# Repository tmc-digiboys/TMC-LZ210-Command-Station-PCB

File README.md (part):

[🇬🇧 English](README.md) | [🇩🇪 Deutsch](README.de.md) | [🇳🇱 Nederlands](README.nl.md)

# DCC Command Station LZ210-TMC

Modular DCC command station with Ethernet and USB connectivity, and (partial) support for the XpressNet and Z21 protocols. The board supports LocoNet-T and XpressNet handhelds and other equipment, provides an interface for external boosters via CDE and LocoNet-B, and has a connection for RS-Bus feedback modules.

## Why this board
The [Twentse Modelspoorweg Club (TMC)](https://twentsemodelspoorweg.club) is modernising its electronics and software for digital layout control. For each of its stations (Hengelo, Enschede, Oldenzaal, Almelo) it needs its own new DCC command station to operate all turnouts and signals, and to receive occupancy feedback. Although DCC command stations are of course available ready-made, building your own is not only a nice challenge, but also a potential cost saving.

The starting point is a modular design, similar to the [Z21PG](https://pgahtow.de/w/Zentrale_Z21PG/de). Initially we looked at whether we could simply adapt or replicate this design. We quickly realised that upgrading to a modern processor and ready-made modules would lead to better results and a lower price.

The goal is to develop a command station that can be extended step by step and that **club members and other interested persons can easily adapt and rebuild**. That is why we deliberately chose an easy-to-solder, low-cost THT (Through-Hole Technology) PCB, and, for the critical components, ready-made modules that can easily be bought online.

For the processor we chose the RP2350B, mainly because of its PIO peripheral, which allows a fully jitter-free DCC signal to be generated. It is an inexpensive and modern dual-core processor, running at 125 MHz. See [processor choice](docs/processor.md) for a comparison with ESP32, DxCore and STM32.

The name LZ210-TMC was chosen as a contraction of Z21 (Roco, Z21 protocol, LocoNet) and LZ100 (Lenz, XpressNet, RS-Bus interface and CDE booster connection).

## Schematic
The complete schematic (all hierarchical sheets) is available in [Schematic.pdf](docs/Schematic.pdf).

The schematic is divided into the following functional blocks (click the name for more details):

<details>
<summary><strong>Power supply</strong></summary>

The command station must be powered with a DC voltage equal to the desired track voltage. In practice, a switching or laptop-style power supply can be used that can deliver a voltage between 14 and 20 volts, and 3 to 4 amps.

⚠️ **Note:** not every switching power supply is suitable or safe for this purpose. Practical advice: choose a power supply of the kind used with other DCC command stations, for example the [Roco 10851](https://www.roco.cc/rde/10851-schaltnetzteil-54-watt.html) or [YaMoRC YD7460-18](https://yamorc.de/products/?singleproduct=13843).

The external supply voltage enters via a 3 amp eFuse and a so-called "ideal diode", which protects the circuit against reverse polarity, and then feeds VCC and two step-down converter modules.

VCC powers the H-bridges for the track voltage and the programming track. VCC also runs to the processor, so that a resistor divider and an ADC input can be used to check whether the external supply voltage has the correct value.

The 12V step-down converter supplies power to LocoNet, XpressNet, the CDE booster interface, and RS-Bus feedback. The 12V voltage is likewise, for monitoring purposes, fed through a resistor divider to an ADC input.

The choice of the 5V step-down converter requires some explanation, because the processor and peripherals actually expect 3V3. The reason 5V was chosen is that the Olimex RP2350 Pico2-XL module already has its own step-down chip on board. An external 3V3 converter must *not* be connected to the 3V3 output of the Olimex module (see below). The output of the Olimex module does deliver enough power to supply the rest of the peripherals with 3V3. The diode between the 5V step-down converter and the Olimex RP2350 Pico2-XL module prevents damage from occurring if, in addition to the external supply, power is also being supplied via the USB connector.

><details>
><summary>Explanation: why not an external 3V3 on the Olimex module?</summary>
>
> The TPS62A02A chip on the Olimex module has active output discharge: as soon as the TPS62A02A is switched off (for example by pulling 3V3_EN to GND), an internal FET is switched on to actively discharge the energy still stored in the external inductor. If, in that state, 3.3V is nevertheless applied to the output of the TPS62A02A, the internal FET keeps conducting and draws tens of mA from the external supply. This can cause the SOT-563 package to overheat. This behaviour is also described on [TI's E2E forum](https://e2e.ti.com/support/power-management-group/power-management/f/power-management-forum/1305135/tps62a01-active-output-discharge).
>
> Hence the choice to feed not the 3V3 output but the VSYS input. This keeps the onboard TPS62A02A always active, regardless of whether power comes from the 5V step-down converter or from USB. The TPS62A02A can deliver enough power to also supply the remaining peripherals.
>
> This behaviour differs from the original Raspberry Pi Pico2: that board uses the RT6150B as its step-down converter, which does not have this active output discharge. On the Pico2, pulling 3V3_EN to GND and then applying an external 3.3V to the output is in fact the method documented by Raspberry Pi itself. For other RP2350B modules: always check which step-down converter is fitted first, since behaviour can differ per board.
>
> </details>

</details>

<details>
<summary><strong>Processor</strong></summary>

We chose a Raspberry Pi Pico processor; see [processor choice](docs/processor.md) for details. An important advantage of the Raspberry Pi Pico is that it has a Programmable IO (PIO) peripheral, a specialised co-processor that can generate very precisely timed output signals.

Within the Pico series there are two variants: the RP2040, with two PIOs, and the RP2350, with three PIOs. Because we use three PIOs, we chose the RP2350. The first PIO is used for the DCC signal, the second for the RS-Bus master, and the third for the XpressNet RS-485 connection.

The RP2350 in turn comes in two variants: the "plain" RP2350, which has 30 General Purpose IO (GPIO) pins, and the RP2350B, which has 18 more. For an early test version of the command station the "plain" RP2350 was used, but because we wanted to use more IO pins we ultimately chose the RP2350B.

Several suppliers (such as Olimex, Waveshare and WeAct) offer different RP2350B modules. We chose the RP2350B-X(X)L module from Olimex; see the reasoning below under Building.

><details>
><summary>Explanation: are alternative modules possible?</summary>
>
> If fewer pins and fewer PIOs are needed — for example because there is no need for an RS-Bus master or XpressNet — RP2040 modules can also be used. In that case, the PCB layout and possibly the power supply would need to be adapted.
>
> </details>

><details>
><summary>Explanation: why a PIO for XpressNet?</summary>
>
> On most processors it is possible to use a UART to send and receive XpressNet messages. That works because the UART on many processors supports both 8 and 9 data bits. XpressNet, however, requires 9 data bits (where the ninth bit indicates whether it is an address or a data byte). Compared with other processors, the UART on the Raspberry Pi Pico is relatively limited and only supports 8 data bits. By writing a small PIO program, it is nevertheless possible to work with 9 data bits on the Raspberry Pi Pico as well, and so support XpressNet.
>
> It would in principle be possible, with some tricks, to still use the UART on the Raspberry Pi Pico for XpressNet. However, since there are only two UARTs, we decided against this.
>
> </details>

</details>

<details>
<summary><strong>Ethernet</strong></summary>

The Ethernet schematic contains only the WIZnet W5500 module. All pins are wired through to the processor.

The older (and often more expensive) W5100 and W5100S modules will probably also work, but this has not been tested.

</details>

<details>
<summary><strong>Track output</strong></summary>

The DCC signal is amplified by a DRV8874 module, fitted with the same driver IC that is also used in the DCC-EX project.

The schematic contains few components because the module itself already contains a number of resistors that result in settings usable for our command station.

By default, I<sub>TRIP</sub> is set to approximately 3 amps. If desired, a different value can be chosen by removing the 2.49 kΩ resistor on the module and fitting R601 with a different value.

By default, **PMODE** is connected to 3V3, which activates PWM mode. If desired, the "PWM (PH / EN) solder jumper" on the bottom of the PCB can be used to connect **PMODE** to GND instead. To do this, remove the existing copper connection to 3V3 to avoid a short circuit, and make the other solder connection to GND.

By default, the module is set to Quad-Level 2, but this can be changed via a second "solder jumper" on the bottom of the PCB by connecting **IMODE** to GND. See the DRV8874 datasheet for the differences between the modes.

No space has been reserved on the PCB for a snubber circuit and/or power inductor. If desired, these can be placed after the connector, in the wiring to the rails.

Detailed background information on the choice and limitations of this driver IC is described on a separate page. That page discusses in detail the inrush-current problems that this and similar chips can have with capacitive loads. See: [DRV8874 output stage](docs/DRV8874.md)

How overcurrent faults (OCP and ITRIP) show up on the **nFAULT** pin, how the processor handles them, and which value of the sense resistor is recommended, is described in [Dealing with nFAULTs](docs/nFault.md).

</details>

<details>
<summary><strong>Programming track</strong></summary>

The PCB allows you to use the same DRV8874 H-bridge module as for the normal track output. The advantage of reusing modules is a uniform parts list and easier building.

However, it is better to use a DRV8876 module instead of a DRV8874 module. These modules can deliver somewhat less power, which is actually an advantage for a programming track, and they are also somewhat cheaper.

An important technical difference between the DRV8874 and DRV8876 modules is that the latter has a higher current-mirror gain factor **AIPROPI**, namely 1000 (instead of 450). As a result, the voltage seen by the processor's ADC input during a (60 mA) DCC-ACK signal is 150 mV (instead of 67 mV). This allows a more reliable measurement of the DCC-ACK signal.

As with the normal track output, it is possible to remove the 2.49 kΩ resistor fitted by default on the module and replace it with R801. A good value for R801 is 6.8 kΩ. With this value, the maximum current I<sub>TRIP</sub> that can be delivered during programming is limited to 500 mA. RCN-216 recommends a (non-mandatory) limit of 250 mA ±20% at power-up, but also permits fixed current limiters up to 1 A; 500 mA fits comfortably within that.

An additional advantage of replacing the 2.49 kΩ resistor with a 6.8 kΩ resistor is that the voltage during a DCC-ACK is increased to well over 400 mV, making it easier to measure on the processor's ADC input.

</details>

<details>
<summary><strong>CDE booster interface</strong></summary>

The PCB uses the same type of H-bridge module as for the programming track (DRV8876 or DRV8874). Technically, a DRV8871 module from AliExpress could also be used. However, the dimensions of this module do not fit the current PCB.

For the CDE output, the well-known inrush-current problems of the DRV887x ICs do not apply. The load is not capacitive, and the CDE signal requires no more than a few hundred milliamps. The internal short-circuit protection of the DRV887x does not trigger during start-up, unless the output is genuinely short-circuited. The DRV887x is oversized for this purpose, but can in principle be used without issue.

Detailed information about the CDE interface is described on a separate page: [CDE interface](docs/CDE.md).

</details>

<details>
<summary><strong>LocoNet</strong></summary>

The schematic for the LocoNet section is standard, and described in many places online. However, the values of a number of components have been adapted so that the whole works on 3V3 as well.

In addition to the LocoNet-T interface, there is also a LocoNet-B interface, which supplies a RailSync signal for boosters via the outermost pins of the connector. The RailSync signal can be generated in several ways.

- Up to and including V2.2, a design was used that was copied from the Internet (https://www.fucik.name/masinky/NanoL/, https://oshwlab.com/fiorinid/z21pg-by-df-pro). These circuits utilise a specialised driver IC; the diagram lists a number of options. Of the options listed, only the UCC27425 IC has an ENABLE input, which allows the RailSync signal to be easily disabled. Resistors rated at 33 Ω / 2 Watt (or preferably 22 Ω / 5 Watt) are connected to the outputs of this driver. On the one hand, these resistors serve as short-circuit protection (which is why they must be capable of dissipating 2 to 5 Watt). On the other hand, these resistors, together with the 4.7 nF capacitors, form a low-pass filter, thus reducing interference. The P6KE15A are ESD diodes that protect the LocoNet driver IC. The disadvantage of this circuit is that it cannot supply more than 100 mA, which limits the maximum number of boosters that can be connected to approximately 10, depending on the type of booster.

- From version 2.3 onwards, RailSync uses the CD(E) (booster) signal. This not only reduces the number of components required (thereby lowering costs), but also allows a much larger number of boosters to be connected. Furthermore, all connected boosters now have exactly the same signal, regardless of whether they are connected via CDE or via LocoNet-T.

</details>

<details>
<summary><strong>XpressNet</strong></summary>

The XpressNet interface is simple and standard. The [OpenDCC site](https://www.opendcc.de/elektronik/opendcc/xpressnet_hw.html) has a basic circuit that many have built. The only change is that the 1K5 resistors have been replaced with 560 Ω, because the driver IC is powered not from 5V but from 3V3. The 8K2 resistor (R504) ensures the driver starts in RX mode.

A MAX(3)485 IC is often used as the driver. A better choice is the MAX(3)483, the slew-rate-limited version of this driver, since it limits possible high-frequency interference on the RS-485 line. Unfortunately, this IC is noticeably more expensive. The OpenDCC page mentioned above gives further details on possible alternative driver ICs.

</details>

<details>
<summary><strong>RS-Bus feedback</strong></summary>

The schematic for the RS-Bus was taken from the [Der-Moba website](https://www.der-moba.de/index.php/RS-Rückmeldebus).
The transistor for transmitting mentioned there has, however, been replaced with an (IRLZ44) MOSFET, allowing for a somewhat higher load.

</details>

## Building
To build the command station, the easiest approach is to have the current PCB manufactured by sending the file [production/TMC-Centrale.zip](production/TMC-Centrale.zip) to a company such as JLCPCB. This file contains all the (Gerber) files the manufacturer needs. In the summer of 2026, having 5 PCBs made, including shipping, cost approximately €25.

The design is open source. Building, modifying, and distributing is encouraged under the terms of the [licence](LICENSE), and with reference to this source.

The complete list of components is: [production/bom.csv](production/bom.csv).

To make building as easy as possible, we chose, wherever possible, ready-made modules of the kind sold online by AliExpress and others. Below is an overview of the main modules, as well as the connectors that fit the PCB:

<details>
<summary><strong>RP2350B (MCU module)</strong></summary>

For the processor we chose the [Olimex RP2350B-XL](https://www.olimex.com/Products/RaspberryPi/PICO/PICO2-XXL/open-source-hardware) module. Olimex guarantees that production of these modules will be supported until at least 2035, and has published all KiCad design files and manufacturing files openly on GitHub.

There are two variants of this module: the RP2350B-XL (€5) and the RP2350B-XXL (€9). The difference is that the XXL has some extra capabilities that are not needed for this command station. Although the schematic references the XXL, the XL variant is preferred for its price. Both variants fit the PCB, however.

The modules can be bought from [Olimex](https://www.olimex.com/Products/RaspberryPi/PICO/PICO2-XXL/open-source-hardware) directly, but also via distributors such as [TME](https://www.tme.eu).

</details>

<details>
<summary><strong>DRV8874 / DRV8876 (motor drivers)</strong></summary>

Ready-made DRV8874 / DRV8876 modules are used for the DCC, programming track, and CDE outputs.

Pololu brought modules for the [DRV8874](https://www.pololu.com/product/4035) and [DRV8876](https://www.pololu.com/product/4037) to market some years ago. Since spring 2026, (cheaper) variants have also become available on AliExpress. The Pololu module includes an extra reverse-polarity-protection MOSFET as additional protection, which the AliExpress modules lack. This extra protection is not needed for this command station.

</details>

<details>
<summary><strong>Step-down module (5V/12V)</strong></summary>

The PCB footprint dimensions are matched to the well-known MP1584 step-down modules, offered by multiple suppliers on AliExpress. Two modules are needed. The first supplies the 5V supply voltage for the processor (note: the Olimex processor module itself converts this 5V to 3V3 again), and the second module supplies 12V. Instead of modules with a fixed 5V/12V output voltage, adjustable-output modules can also be used.

Modules other than the MP1584 will in principle also work, but do not fit the PCB footprint.

</details>

<details>
<summary><strong>Ideal-diode module</strong></summary>

An XL74610 module is used for reverse-polarity protection, as sold on AliExpress and by other suppliers.

</details>

<details>
<summary><strong>W5500 Ethernet</strong></summary>

A W5500 module is used for the Ethernet connection, as sold on AliExpress and by other suppliers.

</details>

<details>
<summary><strong>Connectors</strong></summary>

The PCB is designed for the following connectors:

><details>
><summary>LocoNet: 6P6C (RJ12)</summary>
>
> There are several brands and types of 6P6C connectors on the market, with different footprints. The PCB is designed for connectors with a footprint matching the WayConn MJEA connectors. These have their electrical connections on the bottom (PCB side).
> 
>
> </details>
><details>
><summary>Barrel Jack</summary>
>
> A 5.5x2.1mm barrel jack is used for the power connector.
> 
>
> </details>
><details>
><summary>Terminal Blocks</summary>
>
> A PhoenixContact MSTBA 2.5/2-G, with a pin spacing of 5.00 mm, is used for the DCC track output. Terminal blocks with a pin spacing of 5.08 mm will also fit, however.
>
> A Phoenix Contact MC 1.5/2-G-3.81 terminal block is used for the programming output.
>
> A Phoenix Contact MC 1.5/3-G-3.81 terminal block is used for the CDE output.
>
> A Phoenix Contact MC 1.5/2-G-3.81 terminal block is used for the RS-Bus input.
>
> A Phoenix Contact MC 1.5/4-G-3.81 terminal block is used for the XpressNet output. A 5-pin DIN connector is fitted at the front.
>
> Variants of these connectors are offered by several manufacturers, including PTR/Hartmann.
>
> 
>
> </details>

</details>

## Software

The firmware for this command station can be found in its own GitHub repository, and is therefore not discussed further at: [https://github.com/tmc-digiboys/TMC-LZ210-Command-Station](https://github.com/tmc-digiboys/TMC-LZ210-Command-Station)

## Comparison with other command stations

This command station does not stand on its own, but stands in a long tradition of open-source DCC command stations:

<details>
<summary><strong>OpenDCC</strong></summary>

One of the earliest open-source DCC command stations is the [OpenDCC Z1](https://www.opendcc.de/elektronik/opendcc/opendcc.html). This command station was designed twenty years ago by Wolfgang Kufer.
- **Processor.** OpenDCC runs on an 8-bit Atmel AVR (ATmega32 or ATmega644P) at 16 MHz. This command station uses a dual-core RP2350 at 125 MHz with a PIO peripheral, and is therefore orders of magnitude more powerful.
- **Output stage.** OpenDCC uses a fixed H-bridge (STM L6206), theoretically rated at 2.8 A per output, but thermally limited on the PCB to about 1.5 A continuous. This command station uses a DRV8874 module (6 A theoretical), whose current is limited on the module itself to about 2.7 A.
- **Feedback.** OpenDCC supports S88, with an extension for turnout-position feedback. This command station uses RS-Bus and LocoNet.
- **Connection to a PC.** OpenDCC communicates via RS232/USB with a PC, using XpressNet or P50X as the higher-layer protocol; OpenDCC itself has no network or WiFi connection. This command station has, in addition to USB, its own Ethernet connection, and supports XpressNet and Z21 as higher-layer protocols.
- **Boosters.** OpenDCC has no separate interface for external boosters, such as CDE or LocoNet-B.
- **Handhelds.** Like this command station, OpenDCC supports XpressNet handhelds (such as the Roco Multimaus). OpenDCC does not support LocoNet handhelds, however.

The OpenDCC Z1 command station can be seen as a forerunner of open-source DCC command stations. Many of its ideas, circuits, and software have been copied (in adapted form) by others, and are still in use today. However, building the Z1 today no longer seems like a good idea: modern microcontrollers are both cheaper and many times more powerful than the 8-bit ATmega generation on which the OpenDCC Z1 was based at the time.
</details>

<details>
<summary><strong>BiDiB</strong></summary>

[BiDiB](https://www.bidib.org/) can be seen as a successor to the OpenDCC Z1 command station. BiDiB has been developed since 2010 by — again — Wolfgang Kufer, and is brought to market in hardware form by, among others, Fichtelbahn.
- **Architecture.** BiDiB is primarily a bus onto which multiple intelligent components (such as GBMboost/GBM16T/OpenSwitch/IF2) can be connected. It is not a command station in the traditional sense, with a built-in booster and interfaces such as XpressNet, LocoNet and RS-Bus.
- **Processor.** BiDiB implementations are based on the Atmel XMEGA processor. Although this is one of the most powerful 8/16-bit / 32 MHz processors, it is also a fairly old processor and, compared with the dual-core RP2350 / 125 MHz processor of this command station, quite expensive.
- **Building.** BiDiB PCBs are designed for SMD components. Although BiDiB designs are more advanced and of higher quality than those of this (THT) command station, they are also harder to build, adapt and extend.
- **RailCom.** BiDiB excels at receiving, analysing and processing RailCom feedback. This command station offers no support for this.

BiDiB offers a complete ecosystem with a focus on intelligent components and extensive RailCom processing. This command station is primarily a traditional command station like those from Roco and Lenz, communicating via established protocols with equipment from various manufacturers.

</details>

<details>
<summary><strong>Z21PG</strong></summary>

[Z21PG](https://pgahtow.de/w/Zentrale_Z21PG/) is an Arduino-based self-build project by Philipp Gahtow for a low-cost Roco Z21 clone.
- **Ease of building.** Philipp Gahtow himself publishes mainly software (Arduino sketches) and separate schematics for a number of hardware variants (Arduino MEGA, ESP32, ...). Unlike this command station, there is no official Z21PG (KiCad) PCB design. Third-party PCB designs do exist for the Z21PG, however. Both command stations are easy to build.
- **Processor and DCC signal.** The most commonly built Z21PG variant runs on an (older) ATmega2560 (16 MHz), although ESP32 is also mentioned as an option. The DCC signal is generated in software via timer interrupts, not via a dedicated hardware peripheral. This command station uses a (modern) dual-core RP2350 at 125 MHz with a PIO peripheral, more than ten times as fast and with a jitter-free DCC signal.
- **Interfaces.** Z21PG offers connections comparable to the Roco Z21 command station: LAN, X-Bus (XpressNet), L-Bus (LocoNet-T), booster connection, track and programming output. This command station additionally has an RS-Bus connection, and its booster connections are compatible with CDE and LocoNet-B.

Of all the projects discussed here, Z21PG has the most in common with this command station. Both are modularly designed and relatively easy and cheap to build. Z21PG primarily takes the Roco Z21 as its model, whereas this command station also takes the Lenz command stations as a model. Z21PG is a somewhat older design; this command station uses more modern components.
</details>

<details>
<summary><strong>DCC-EX</strong></summary>

A currently popular self-build command station is [DCC-EX](https://dcc-ex.com/). There are functional similarities (including the DRV8874 output stage), but also a number of significant differences:
- **Availability.** DCC-EX offers both factory-assembled boards (EX-CSB1, from approx. €75–115 excl. VAT/shipping) and DIY builds on Arduino form-factor boards. This command station is intended for self-building, and its component cost is lower (approx. €40).
- **Connection to a PC/network.** This command station uses Ethernet (XpressNet and Z21); DCC-EX uses WiFi (with JMRI, WiThrottle and Engine Driver support).
- **Interfaces for handhelds.** This command station has native (RS485) XpressNet and LocoNet interfaces, to which Lenz, Roco and other handhelds can be connected. DCC-EX focuses primarily on WiFi throttles and JMRI.
- **Interfaces for feedback.** This command station has native RS-Bus and LocoNet interfaces. DCC-EX has no such interfaces.
- **Booster interfaces.** This command station supports external boosters via LocoNet-B and the CDE interface. DCC-EX has no CDE/LocoNet-B support, but does have a RailSync mechanism, through which external boosters can be connected.
- **Mixed DCC/DC operation.** DCC-EX can switch each output between DCC and DC PWM, so that classic DC locomotives can run as well. This command station supports DCC only.

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
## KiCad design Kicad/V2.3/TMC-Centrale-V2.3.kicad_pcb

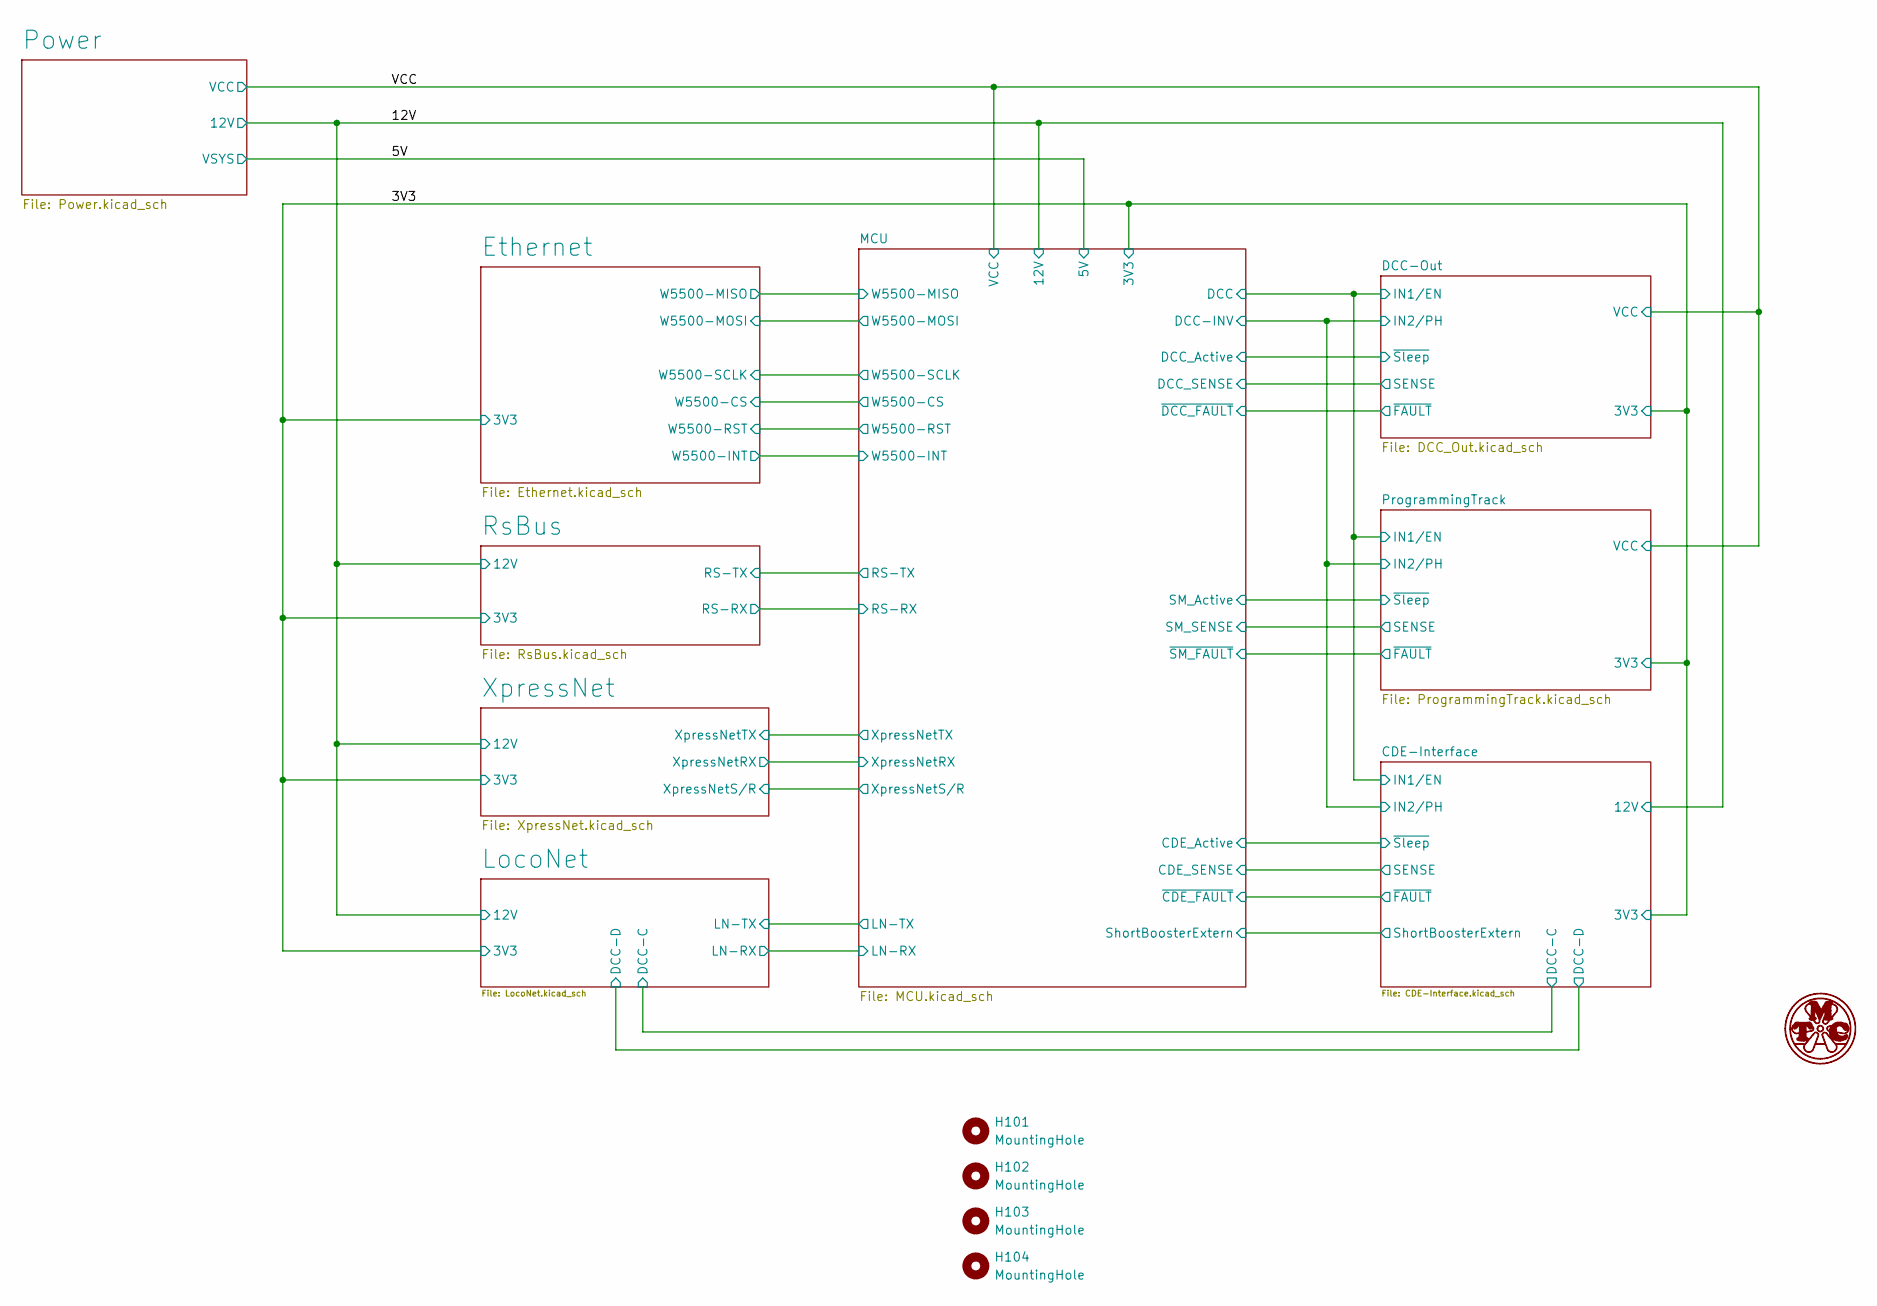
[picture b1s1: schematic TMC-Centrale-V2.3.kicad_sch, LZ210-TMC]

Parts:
H101, H102, H103, H104: MountingHole; MountingHole_3.2mm_M3

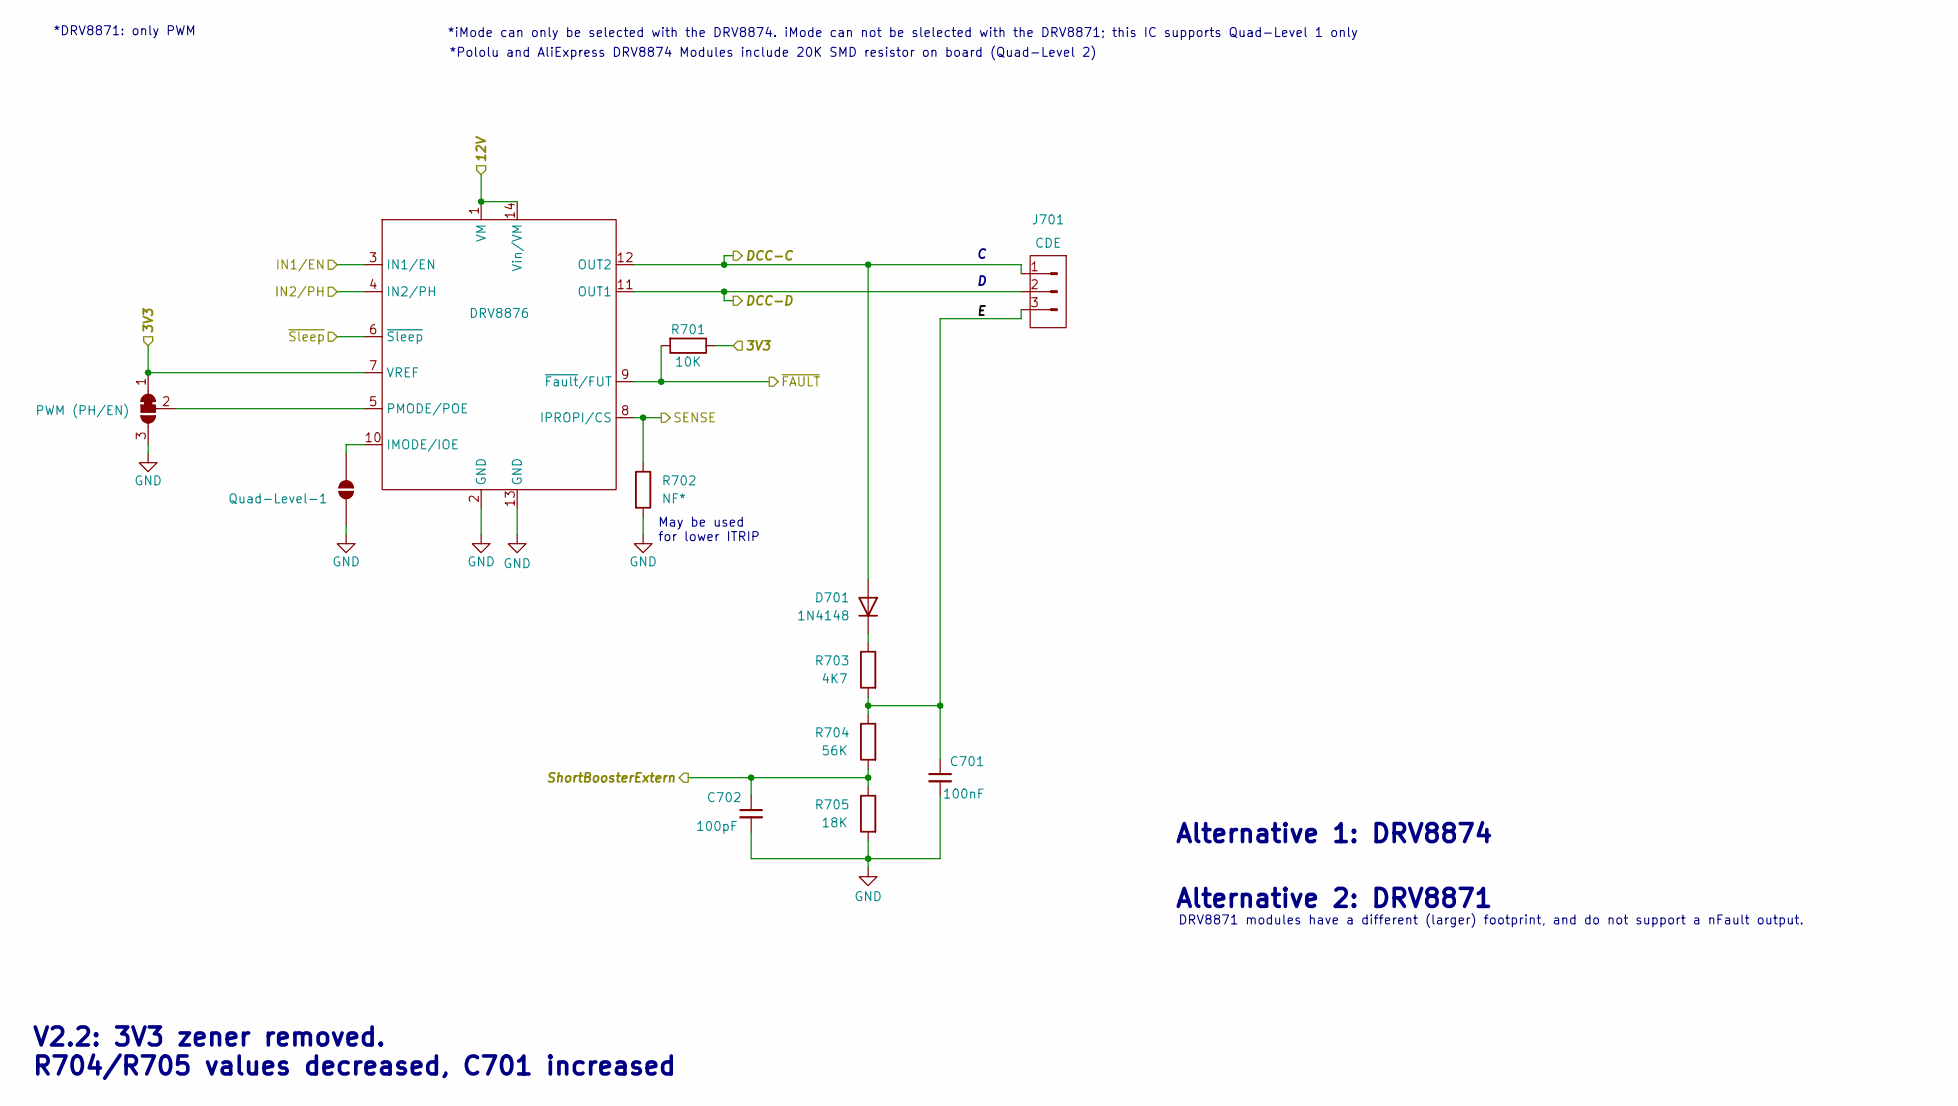
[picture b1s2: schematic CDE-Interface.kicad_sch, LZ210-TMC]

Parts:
C701: 100nF; C_Disc_D5.0mm_W2.5mm_P5.00mm
C702: 100pF; C_Disc_D5.0mm_W2.5mm_P5.00mm
D701: 1N4148; DO35-7
J701: CDE; PhoenixContact_MC_1,5_3-G-3.81_1x03_P3.81mm_Horizontal
JP701: PWM (PH/EN); SolderJumper-3_P1.3mm_Bridged12_RoundedPad1.0x1.5mm_NumberL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
JP702: Quad-Level-1; SolderJumper-2_P1.3mm_Open_RoundedPad1.0x1.5mm
R701: 10K; R-0207-10
R702: NF*; R-0207-10
R703: 4K7; R-0207-10
R704: 56K; R-0207-10
R705: 18K; R-0207-10
U701: DRV8876; Module-DRV8874

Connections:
/3V3: JP701.1 (A), R701.1, U701.7 (VREF); also elsewhere on the board
/12V: U701.1 (VM), U701.14 (Vin/VM); also elsewhere on the board
/CDE-Interface/DCC-C: D701.2 (A), J701.1, U701.12 (OUT2); also elsewhere on the board
/CDE-Interface/DCC-D: J701.2, U701.11 (OUT1); also elsewhere on the board
/CDE-Interface/E: C701.1, J701.3, R703.2, R704.1
/CDE-Interface/IN1/EN: U701.3 (IN1/EN); also elsewhere on the board
/CDE-Interface/IN2/PH: U701.4 (IN2/PH); also elsewhere on the board
/CDE-Interface/SENSE: R702.1, U701.8 (IPROPI/CS); also elsewhere on the board
/CDE-Interface/ShortBoosterExtern: C702.1, R704.2, R705.1; also elsewhere on the board
/CDE-Interface/~FAULT: R701.2, U701.9 (~Fault/FUT); also elsewhere on the board
/CDE-Interface/~Sleep: U701.6 (~Sleep); also elsewhere on the board
GND: C701.2, C702.2, JP701.3 (B), JP702.1 (A), R702.2, R705.2, U701.2 (GND), U701.13 (GND); also elsewhere on the board
unnamed: D701.1 (K), R703.1
unnamed: JP701.2 (C), U701.5 (PMODE/POE)
unnamed: JP702.2 (B), U701.10 (IMODE/IOE)

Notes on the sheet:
*iMode can only be selected with the DRV8874. iMode can not be slelected with the DRV8871; this IC supports Quad-Level 1 only
May be used for lower ITRIP
DRV8871 modules have a different (larger) footprint, and do not support a nFault output.
Alternative 1: DRV8874
*Pololu and AliExpress DRV8874 Modules include 20K SMD resistor on board (Quad-Level 2)
Alternative 2: DRV8871
V2.2: 3V3 zener removed. R704/R705 values decreased, C701 increased
*DRV8871: only PWM

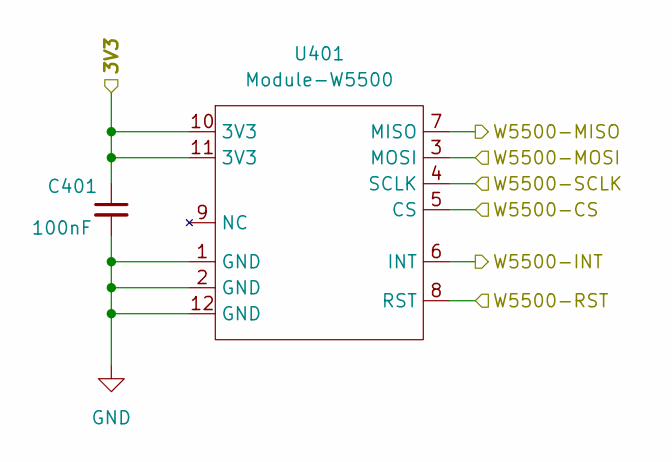
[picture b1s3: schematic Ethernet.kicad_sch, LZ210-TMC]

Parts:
C401: 100nF; C_Disc_D5.0mm_W2.5mm_P2.50mm
U401: Module-W5500

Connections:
/3V3: C401.1, U401.10 (3V3), U401.11 (3V3); also elsewhere on the board
/Ethernet/W5500-CS: U401.5 (CS); also elsewhere on the board
/Ethernet/W5500-INT: U401.6 (INT); also elsewhere on the board
/Ethernet/W5500-MISO: U401.7 (MISO); also elsewhere on the board
/Ethernet/W5500-MOSI: U401.3 (MOSI); also elsewhere on the board
/Ethernet/W5500-RST: U401.8 (RST); also elsewhere on the board
/Ethernet/W5500-SCLK: U401.4 (SCLK); also elsewhere on the board
GND: C401.2, U401.1 (GND), U401.2 (GND), U401.12 (GND); also elsewhere on the board

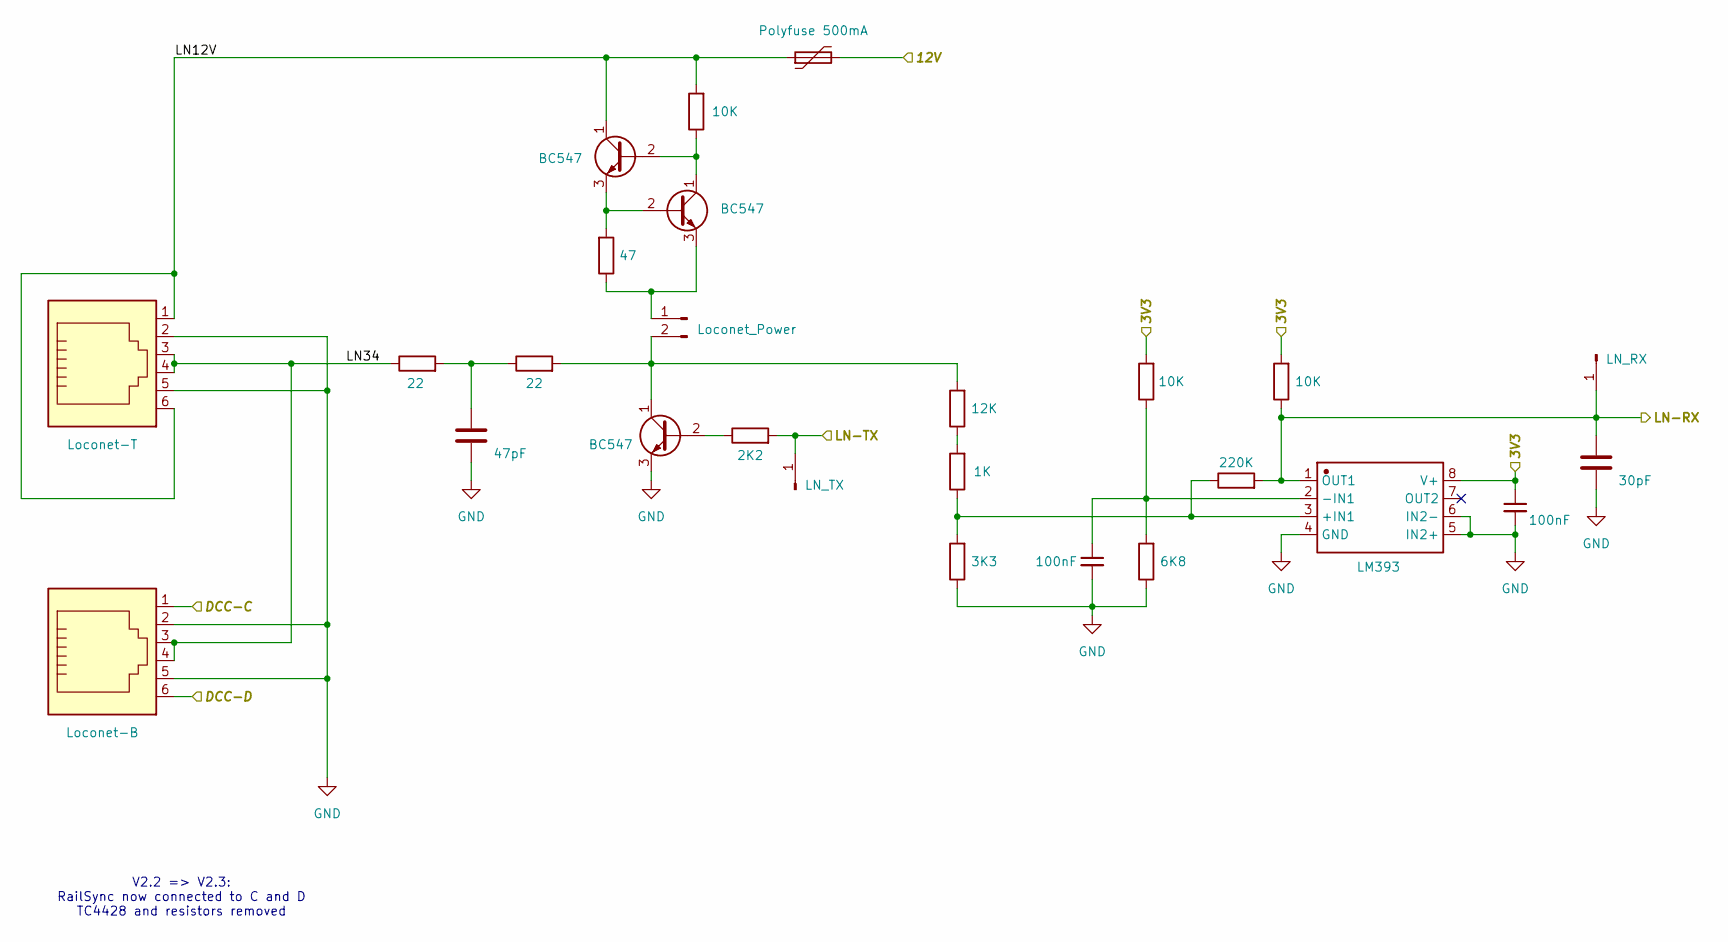
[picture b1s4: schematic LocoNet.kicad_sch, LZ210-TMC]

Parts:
C1001: 47pF; C_Disc_D8.0mm_W2.5mm_P5.00mm
C1002: 30pF; C_Disc_D8.0mm_W2.5mm_P5.00mm
C1003, C1004: 100nF; C_Disc_D5.0mm_W2.5mm_P2.50mm
F1001: Polyfuse 500mA; Fuse_Bourns_MF-RHT050
J1001: Loconet_Power; PinHeader_1x02_P2.54mm_Vertical
J1002: Loconet-T; RJ25_Wayconn_MJEA-660X1_Horizontal
J1003: LN_RX; PinHeader_1x01_P2.54mm_Vertical
J1004: LN_TX; PinHeader_1x01_P2.54mm_Vertical
J1006: Loconet-B; RJ25_Wayconn_MJEA-660X1_Horizontal
Q1001, Q1002, Q1003: BC547; TO-92_BC5xx_HandSolder
R1001, R1005, R1006: 10K; R-0207-10
R1002: 47; R-0207-10
R1003, R1004: 22; R-0207-10
R1007: 12K; R-0207-10
R1008: 2K2; R-0207-10
R1009: 1K; R-0207-10
R1010: 220K; R-0207-10
R1011: 3K3; R-0207-10
R1012: 6K8; R-0207-10
U1001: LM393; DIL08

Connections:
/3V3: C1003.1, R1005.2, R1006.2, U1001.8 (V+); also elsewhere on the board
/12V: F1001.2; also elsewhere on the board
/CDE-Interface/DCC-C: J1006.1; also elsewhere on the board
/CDE-Interface/DCC-D: J1006.6; also elsewhere on the board
/LocoNet/LN12V: F1001.1, J1002.1, J1002.6, Q1001.1 (C), R1001.2
/LocoNet/LN34: J1002.3, J1002.4, J1006.3, J1006.4, R1003.1
/LocoNet/LN-RX: C1002.1, J1003.1 (Pin_1_1), R1006.1, R1010.2, U1001.1 (OUT1); also elsewhere on the board
/LocoNet/LN-TX: J1004.1 (Pin_1_1), R1008.2; also elsewhere on the board
GND: C1001.2, C1002.2, C1003.2, C1004.2, J1002.2, J1002.5, J1006.2, J1006.5, Q1003.3 (E), R1011.1, R1012.1, U1001.4 (GND), U1001.5 (IN2+), U1001.6 (IN2-); also elsewhere on the board
unnamed: C1001.1, R1003.2, R1004.1
unnamed: J1001.1, Q1002.3 (E), R1002.1
unnamed: J1001.2, Q1003.1 (C), R1004.2, R1007.2
unnamed: Q1001.2 (B), Q1002.1 (C), R1001.1
unnamed: Q1001.3 (E), Q1002.2 (B), R1002.2
unnamed: Q1003.2 (B), R1008.1
unnamed: R1007.1, R1009.2
unnamed: R1009.1, R1010.1, R1011.2, U1001.3 (+IN1)
unnamed: C1004.1, R1005.1, R1012.2, U1001.2 (-IN1)

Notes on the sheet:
V2.2 => V2.3: RailSync now connected to C and D TC4428 and resistors removed

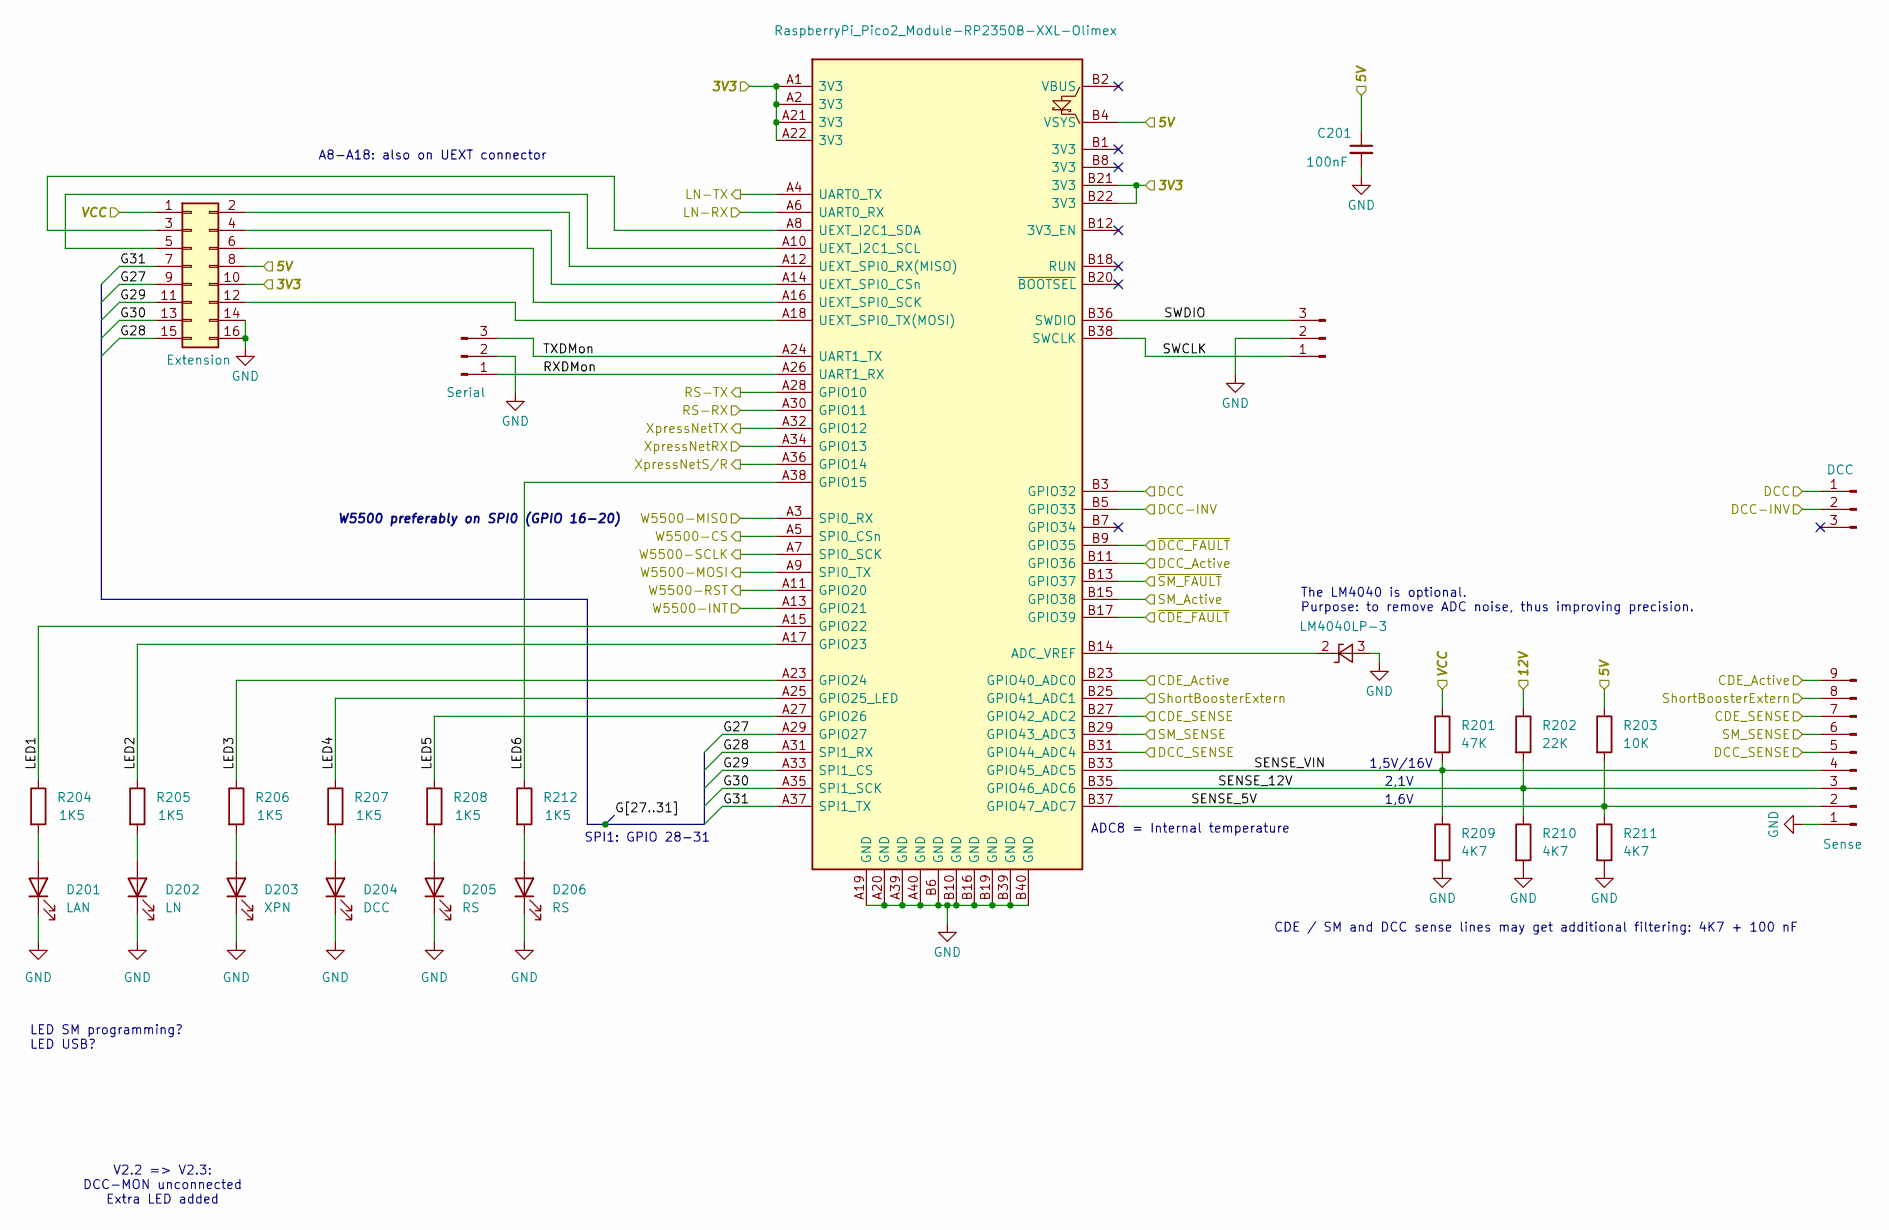
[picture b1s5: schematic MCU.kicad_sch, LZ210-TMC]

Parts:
C201: 100nF; C_Disc_D5.0mm_W2.5mm_P2.50mm
D201: LAN; LED_D3.0mm
D202: LN; LED_D3.0mm
D203: XPN; LED_D3.0mm
D204: DCC; LED_D3.0mm
D205, D206: RS; LED_D3.0mm
J201: Extension; IDC-Header_2x08_P2.54mm_Vertical
J202: Debug; Molex_KK-254_AE-6410-03A_1x03_P2.54mm_Vertical
J203: Serial; Molex_KK-254_AE-6410-03A_1x03_P2.54mm_Vertical
J204: DCC; PinHeader_1x03_P2.54mm_Vertical
J205: Sense; PinHeader_1x09_P2.54mm_Vertical
R201: 47K; R-0207-10
R202: 22K; R-0207-10
R203: 10K; R-0207-10
R204, R205, R206, R207, R208, R212: 1K5; R-0207-10
R209, R210, R211: 4K7; R-0207-10
U201: RaspberryPi_Pico2_Module-RP2350B-XXL-Olimex; Module-RP2350B-XXL-Olimex
U202: LM4040LP-3; TO-92_Inline

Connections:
/3V3: J201.10, U201.A1 (3V3), U201.A2 (3V3), U201.A21 (3V3), U201.A22 (3V3), U201.B21 (3V3), U201.B22 (3V3); also elsewhere on the board
/5V: C201.1, J201.8, R203.1, U201.B4 (VSYS); also elsewhere on the board
/12V: R202.1; also elsewhere on the board
/CDE-Interface/IN1/EN: J204.1, U201.B3 (GPIO32); also elsewhere on the board
/CDE-Interface/IN2/PH: J204.2, U201.B5 (GPIO33); also elsewhere on the board
/CDE-Interface/SENSE: J205.7, U201.B27 (GPIO42_ADC2); also elsewhere on the board
/CDE-Interface/ShortBoosterExtern: J205.8, U201.B25 (GPIO41_ADC1); also elsewhere on the board
/CDE-Interface/~FAULT: U201.B17 (GPIO39); also elsewhere on the board
/CDE-Interface/~Sleep: J205.9, U201.B23 (GPIO40_ADC0); also elsewhere on the board
/DCC-Out/SENSE: J205.5, U201.B31 (GPIO44_ADC4); also elsewhere on the board
/DCC-Out/~FAULT: U201.B9 (GPIO35); also elsewhere on the board
/DCC-Out/~Sleep: U201.B11 (GPIO36); also elsewhere on the board
/Ethernet/W5500-CS: U201.A5 (SPI0_CSn); also elsewhere on the board
/Ethernet/W5500-INT: U201.A13 (GPIO21); also elsewhere on the board
/Ethernet/W5500-MISO: U201.A3 (SPI0_RX); also elsewhere on the board
/Ethernet/W5500-MOSI: U201.A9 (SPI0_TX); also elsewhere on the board
/Ethernet/W5500-RST: U201.A11 (GPIO20); also elsewhere on the board
/Ethernet/W5500-SCLK: U201.A7 (SPI0_SCK); also elsewhere on the board
/LocoNet/LN-RX: U201.A6 (UART0_RX); also elsewhere on the board
/LocoNet/LN-TX: U201.A4 (UART0_TX); also elsewhere on the board
/MCU/G27: J201.9, U201.A29 (GPIO27)
/MCU/G28: J201.15, U201.A31 (SPI1_RX)
/MCU/G29: J201.11, U201.A33 (SPI1_CS)
/MCU/G30: J201.13, U201.A35 (SPI1_SCK)
/MCU/G31: J201.7, U201.A37 (SPI1_TX)
/MCU/LED1: R204.1, U201.A15 (GPIO22)
/MCU/LED2: R205.1, U201.A17 (GPIO23)
/MCU/LED3: R206.1, U201.A23 (GPIO24)
/MCU/LED4: R207.1, U201.A25 (GPIO25_LED)
/MCU/LED5: R208.1, U201.A27 (GPIO26)
/MCU/LED6: R212.1, U201.A38 (GPIO15)
/MCU/RS-RX: U201.A30 (GPIO11); also elsewhere on the board
/MCU/RS-TX: U201.A28 (GPIO10); also elsewhere on the board
/MCU/RXDMon: J203.1, U201.A26 (UART1_RX)
/MCU/SENSE_5V: J205.2, R203.2, R211.1, U201.B37 (GPIO47_ADC7)
/MCU/SENSE_12V: J205.3, R202.2, R210.1, U201.B35 (GPIO46_ADC6)
/MCU/SENSE_VIN: J205.4, R201.2, R209.1, U201.B33 (GPIO45_ADC5)
/MCU/SM_Active: U201.B15 (GPIO38); also elsewhere on the board
/MCU/SM_SENSE: J205.6, U201.B29 (GPIO43_ADC3); also elsewhere on the board
/MCU/SWCLK: J202.1, U201.B38 (SWCLK)
/MCU/SWDIO: J202.3, U201.B36 (SWDIO)
/MCU/TXDMon: J203.3, U201.A24 (UART1_TX)
/MCU/XpressNetRX: U201.A34 (GPIO13); also elsewhere on the board
/MCU/XpressNetS/R: U201.A36 (GPIO14); also elsewhere on the board
/MCU/XpressNetTX: U201.A32 (GPIO12); also elsewhere on the board
/MCU/~SM_FAULT: U201.B13 (GPIO37); also elsewhere on the board
/VCC: J201.1, R201.1; also elsewhere on the board
GND: C201.2, D201.1 (K), D202.1 (K), D203.1 (K), D204.1 (K), D205.1 (K), D206.1 (K), J201.14, J201.16, J202.2, J203.2, J205.1, R209.2, R210.2, R211.2, U201.A19 (GND), U201.A20 (GND), U201.A39 (GND), U201.A40 (GND), U201.B6 (GND), U201.B10 (GND), U201.B16 (GND), U201.B19 (GND), U201.B39 (GND), U201.B40 (GND), U202.3 (A); also elsewhere on the board
unnamed: D201.2 (A), R204.2
unnamed: D202.2 (A), R205.2
unnamed: D203.2 (A), R206.2
unnamed: D204.2 (A), R207.2
unnamed: D205.2 (A), R208.2
unnamed: D206.2 (A), R212.2
unnamed: J201.2, U201.A12 (UEXT_SPI0_RX(MISO))
unnamed: J201.3, U201.A8 (UEXT_I2C1_SDA)
unnamed: J201.4, U201.A14 (UEXT_SPI0_CSn)
unnamed: J201.5, U201.A10 (UEXT_I2C1_SCL)
unnamed: J201.6, U201.A16 (UEXT_SPI0_SCK)
unnamed: J201.12, U201.A18 (UEXT_SPI0_TX(MOSI))
unnamed: U201.B14 (ADC_VREF), U202.2 (K)

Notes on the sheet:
1,5V/16V
LED SM programming? LED USB?
1,6V
The LM4040 is optional. Purpose: to remove ADC noise, thus improving precision.
2,1V
CDE / SM and DCC sense lines may get additional filtering: 4K7 + 100 nF
SPI1: GPIO 28-31
W5500 preferably on SPI0 (GPIO 16-20)
A8-A18: also on UEXT connector
V2.2 => V2.3: DCC-MON unconnected Extra LED added
ADC8 = Internal temperature

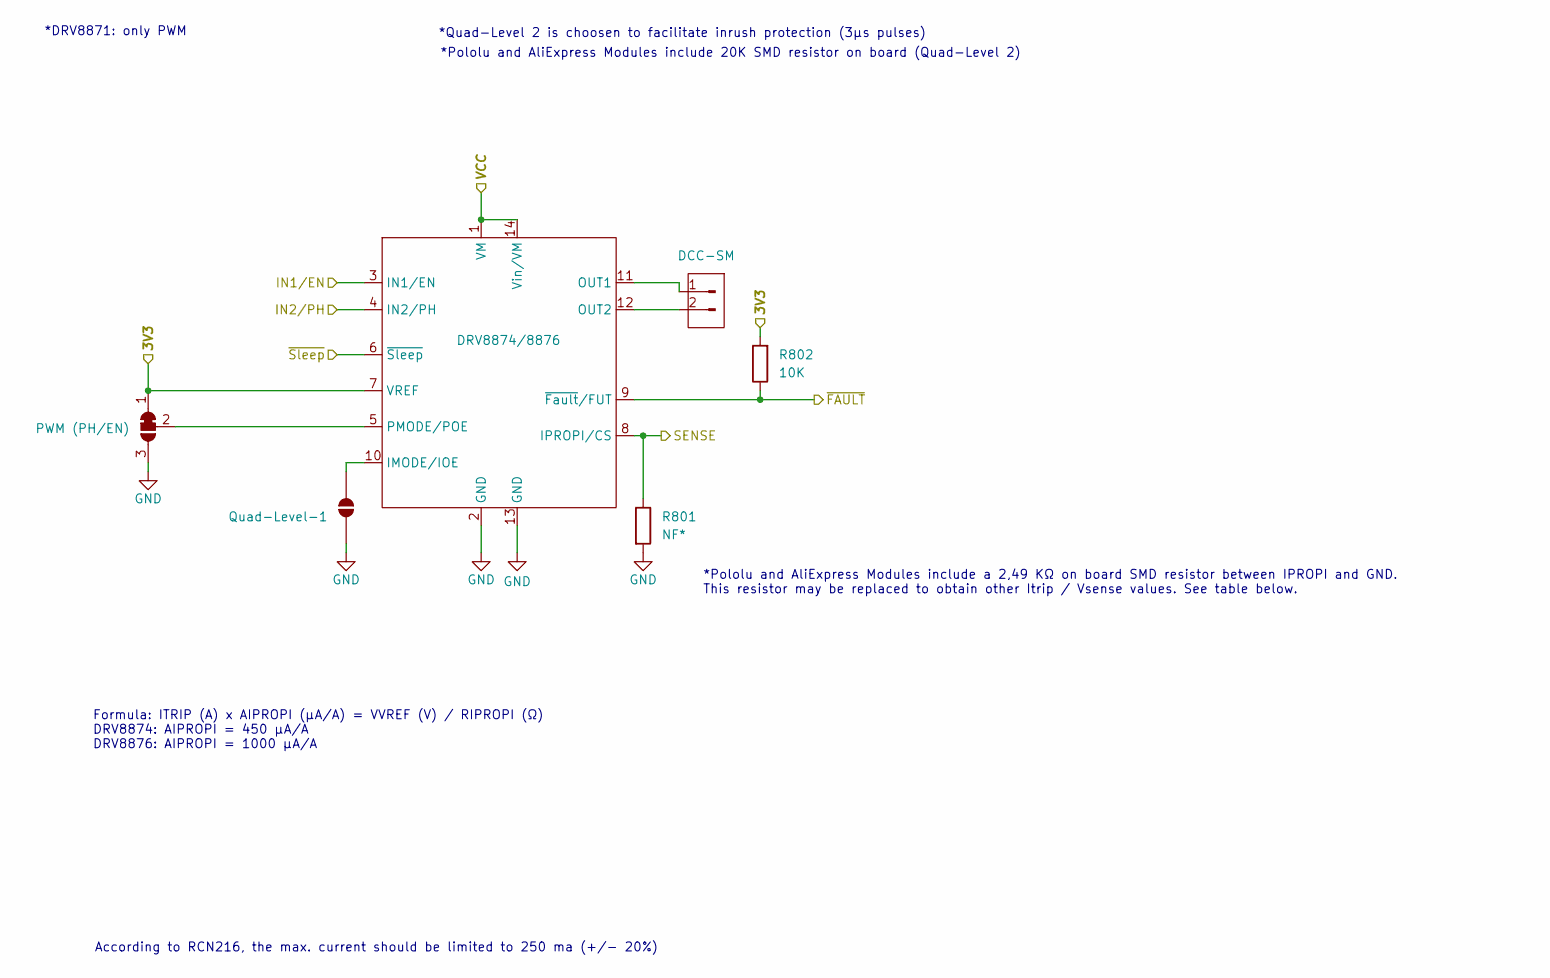
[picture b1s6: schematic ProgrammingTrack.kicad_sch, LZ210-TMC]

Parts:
J801: DCC-SM; PhoenixContact_MC_1,5_2-G-3.81_1x02_P3.81mm_Horizontal
JP801: PWM (PH/EN); SolderJumper-3_P1.3mm_Bridged12_RoundedPad1.0x1.5mm_NumberL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
JP802: Quad-Level-1; SolderJumper-2_P1.3mm_Open_RoundedPad1.0x1.5mm
R801: NF*; R-0207-10
R802: 10K; R-0207-10
U801: DRV8874/8876; Module-DRV8874

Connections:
/3V3: JP801.1 (A), R802.2, U801.7 (VREF); also elsewhere on the board
/CDE-Interface/IN1/EN: U801.3 (IN1/EN); also elsewhere on the board
/CDE-Interface/IN2/PH: U801.4 (IN2/PH); also elsewhere on the board
/MCU/SM_Active: U801.6 (~Sleep); also elsewhere on the board
/MCU/SM_SENSE: R801.1, U801.8 (IPROPI/CS); also elsewhere on the board
/MCU/~SM_FAULT: R802.1, U801.9 (~Fault/FUT); also elsewhere on the board
/VCC: U801.1 (VM), U801.14 (Vin/VM); also elsewhere on the board
GND: JP801.3 (B), JP802.1 (A), R801.2, U801.2 (GND), U801.13 (GND); also elsewhere on the board
unnamed: J801.1, U801.11 (OUT1)
unnamed: J801.2, U801.12 (OUT2)
unnamed: JP801.2 (C), U801.5 (PMODE/POE)
unnamed: JP802.2 (B), U801.10 (IMODE/IOE)

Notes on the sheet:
*Quad-Level 2 is choosen to facilitate inrush protection (3µs pulses)
*DRV8871: only PWM
According to RCN216, the max. current should be limited to 250 ma (+/- 20%)
*Pololu and AliExpress Modules include a 2,49 KΩ on board SMD resistor between IPROPI and GND. This resistor may be replaced to obtain other Itrip / Vsense values. See table below.
*Pololu and AliExpress Modules include 20K SMD resistor on board (Quad-Level 2)
Formula: ITRIP (A) x AIPROPI (μA/A) = VVREF (V) / RIPROPI (Ω) DRV8874: AIPROPI = 450 μA/A DRV8876: AIPROPI = 1000 μA/A

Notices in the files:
Kicad/CDE-Interface.kicad_sch:
Licensed under CC-BY-4.0 — https://creativecommons.org/licenses/by/4.0
Copyright (c) 2026: Aiko Pras / Rob van Hoeijen
